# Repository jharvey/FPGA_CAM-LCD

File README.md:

## Phase order (do not skip)

1. Cleanup / hierarchy (done / finishing)
2. Power input redesign (3×18650)
3. Camera + display connectors/sheets
4. Mechanical outline / placement
5. BOM + JLCPCB

## When unsure

- Ask before deleting anything on `power`, `usb`, `ram`, `flash`, or `wifi`.
- Prefer “mark for deletion” + commit message over silent large deletes.
- Reference `ROADMAP.md` for locked decisions.

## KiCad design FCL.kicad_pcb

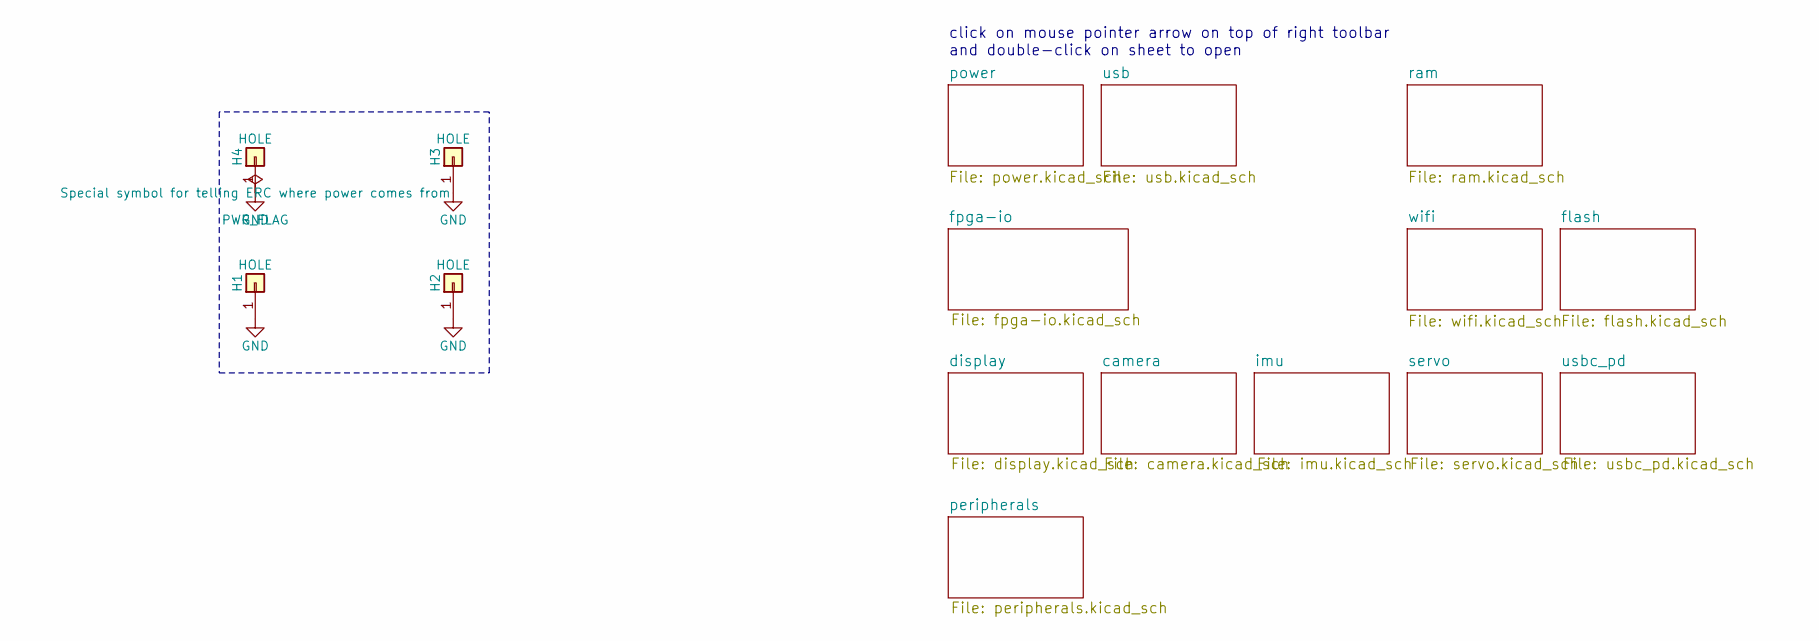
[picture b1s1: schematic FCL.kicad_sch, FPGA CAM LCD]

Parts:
H1, H2, H3, H4: HOLE; MountingHole_3.2mm_M3_ISO14580_Pad

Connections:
GND: H1.1 (Pin_1_1), H2.1, H3.1 (Pin_1_1), H4.1 (Pin_1_1); also elsewhere on the board

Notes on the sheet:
click on mouse pointer arrow on top of right toolbar and double-click on sheet to open

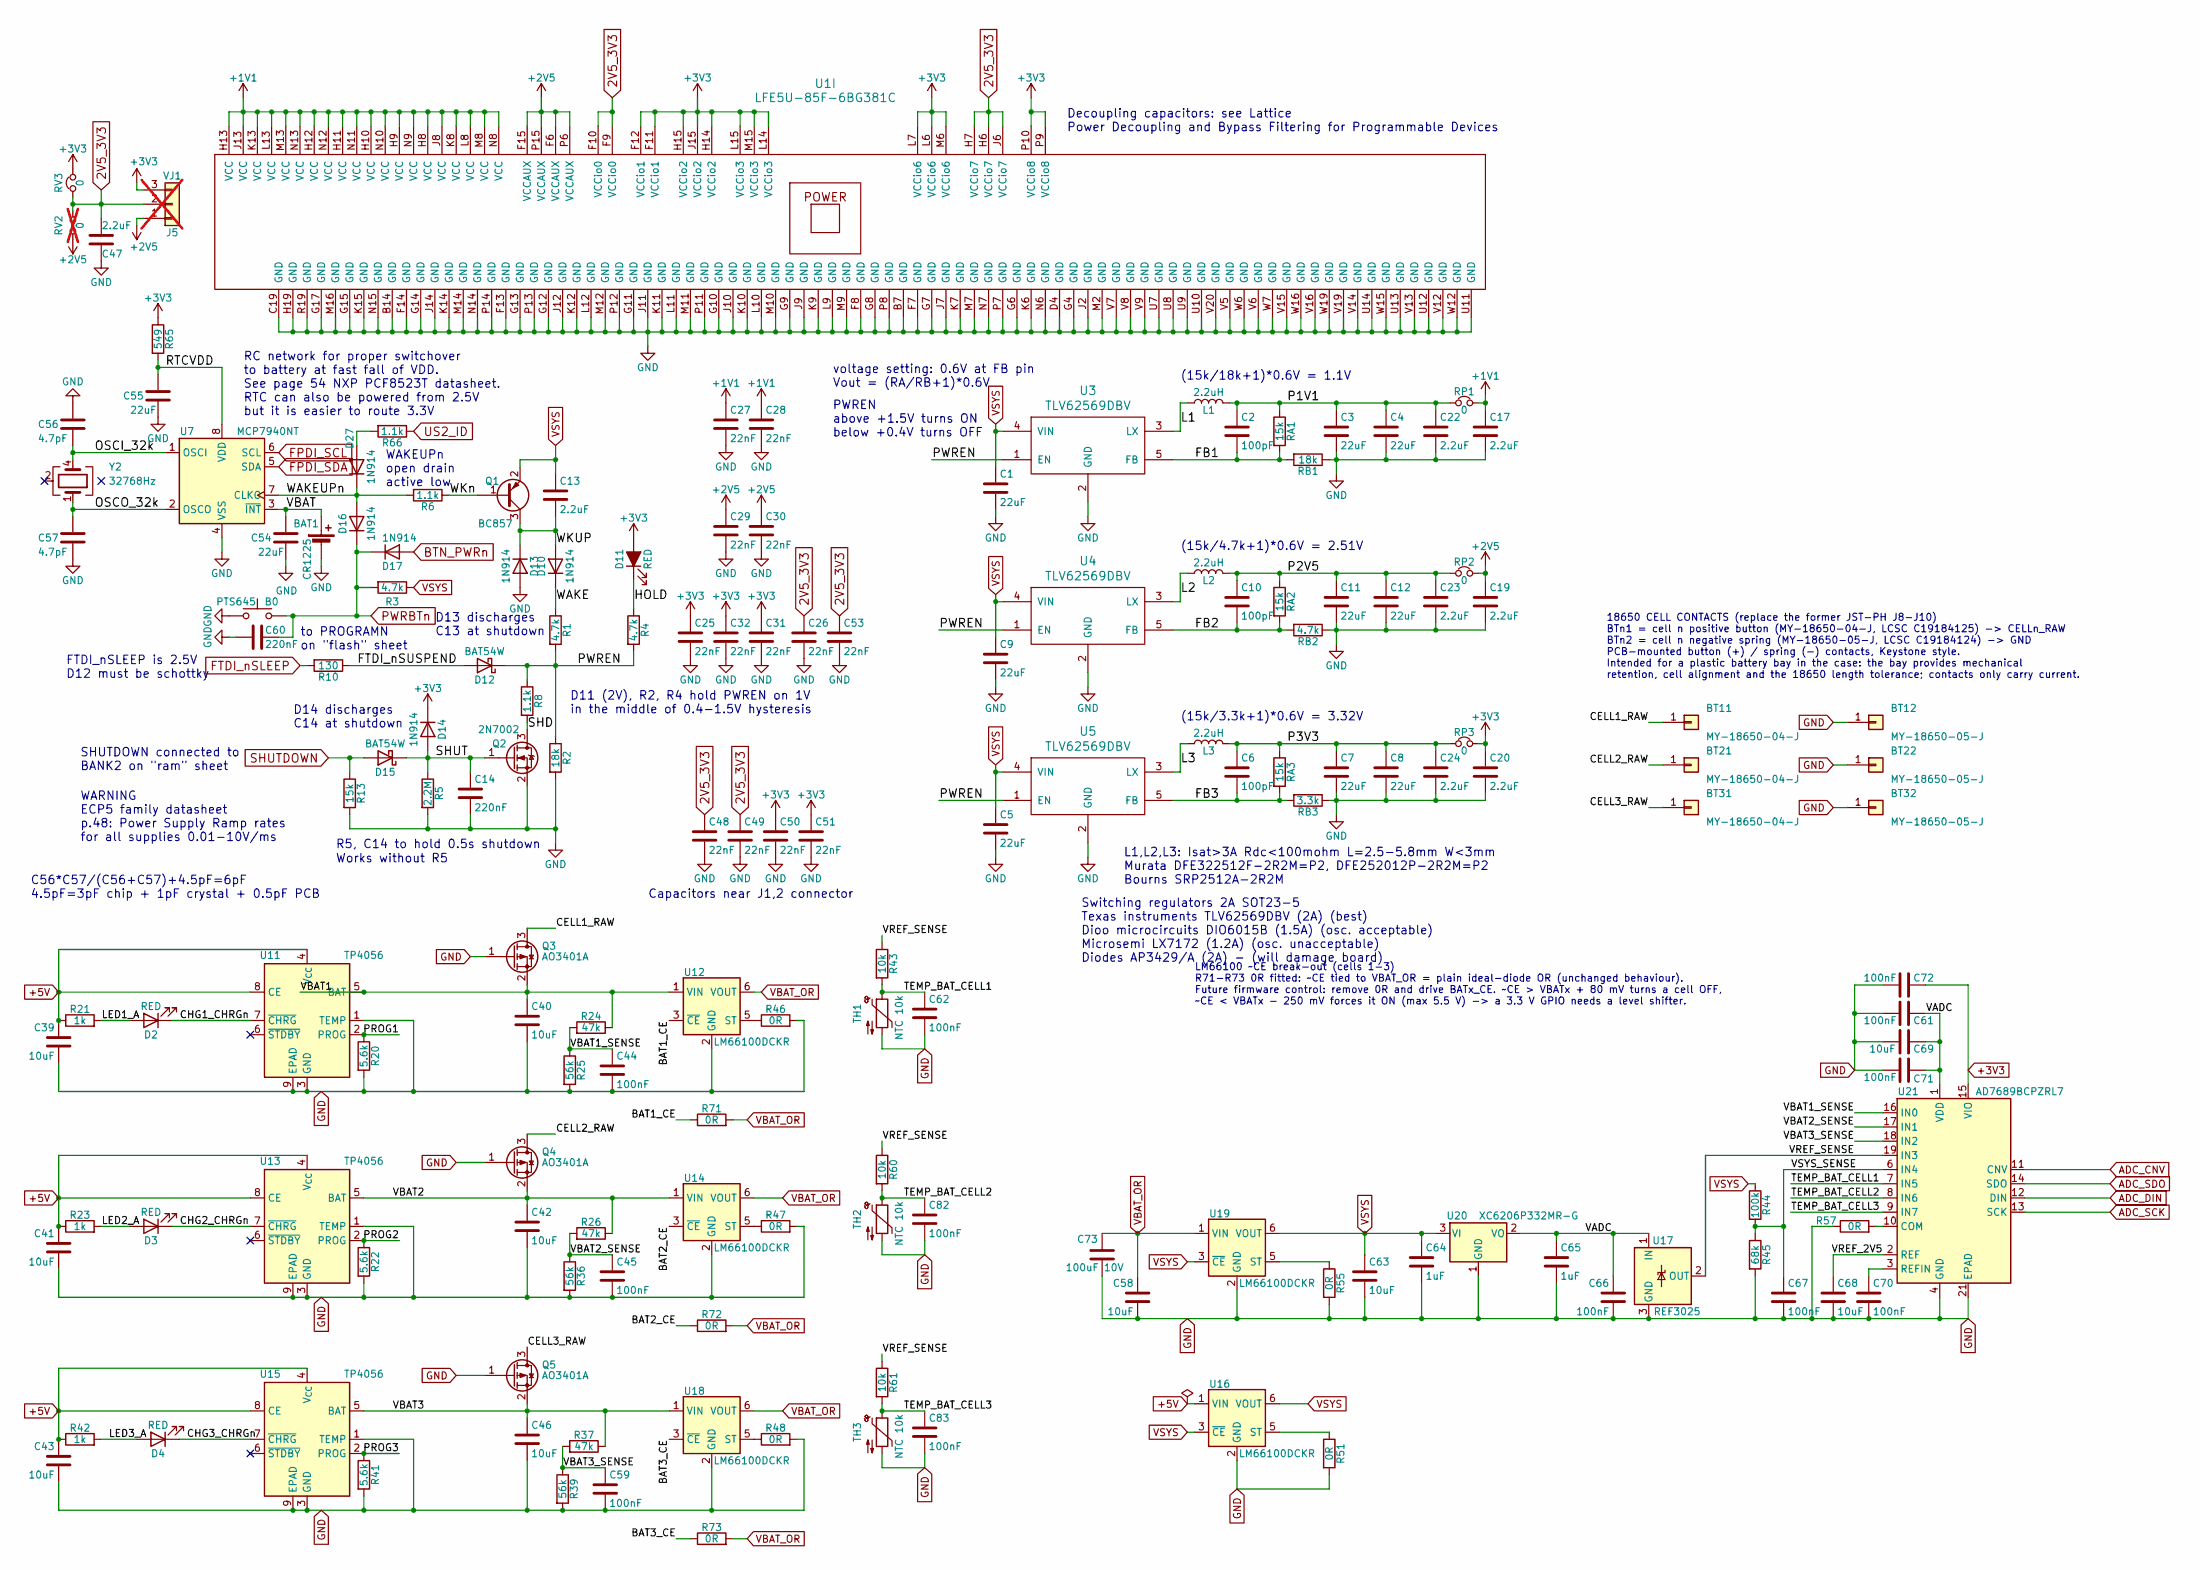
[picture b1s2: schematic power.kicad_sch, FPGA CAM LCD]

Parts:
B0: PTS645; SW_SPST_PTS645Sx43SMTR92; MPN PTS645SL50SMTR92 LFS; Mouser 611-PTS645SL50SMTR92
BAT1: CR1225; Keystone_3000_1x12mm-CoinCell; MPN 3000TR; Mouser 614-SMTM1225.TR
BT11, BT21, BT31: MY-18650-04-J; BAT-TH_MY-18650-04-J; MPN MY-18650-04-J; LCSC C19184125
BT12, BT22, BT32: MY-18650-05-J; BAT-TH_MY-18650-05-J; MPN MY-18650-05-J; LCSC C19184124
C1: 22uF; C_0805_2012Metric; MPN CC0805ZKY5V5BB226; Mouser 81-GRM21BR61A226ME1L
C2: 100pF; C_0603_1608Metric; MPN CS0603KRX7R9BB471; Mouser 581-06035A101JAT4A
C3, C4, C7, C8, C11, C12: 22uF; C_0805_2012Metric
C5, C9, C54, C55: 22uF; C_0805_2012Metric; MPN CC0805ZKY5V5BB226
C6, C10: 100pF; C_0603_1608Metric
C13: 2.2uF; C_0805_2012Metric; MPN CC0805MRX5R6BB225; Mouser 187-CL21B225KOFNNNG
C14: 220nF; C_0603_1608Metric; MPN CC0603KRX7R8BB224; Mouser 603-CC603KRX7R6BB224
C17, C19, C20, C22, C23, C24: 2.2uF; C_0805_2012Metric
C25: 22nF; C_0603_1608Metric; MPN CC0603JRX7R8BB223; Mouser 603-CC603KRX7R7BB223
C26, C27, C28, C29, C30, C31, C32, C48, C49, C50, C51, C53: 22nF; C_0603_1608Metric; MPN CX0603MRX7R8BB223
C39, C40, C41, C42, C43, C46, C58, C63, C68, C69: 10uF; C_0805_2012Metric; LCSC C15850
C44, C45, C59, C61, C62, C66, C67, C70, C71, C72, C82, C83: 100nF; C_0402_1005Metric; LCSC C1525
C47: 2.2uF; C_0805_2012Metric; MPN CC0805MRX5R6BB225
C56: 4.7pF; C_0603_1608Metric; MPN CC0603CRNPO9BN3R3; Mouser 603-CC603CPNPO9BN4R7
C57: 4.7pF; C_0603_1608Metric
C60: 220nF; C_0603_1608Metric
C64, C65: 1uF; C_0603_1608Metric; LCSC C15849
C73: 100uF 10V; C_1210_3225Metric; MPN CL32A107MPVNNNE; LCSC C23742
D2, D3, D4: RED; LED_0603_1608Metric; LCSC C2286
D10, D13, D14, D17, D27: 1N914; D_SOD-323_HandSoldering
D11: RED; LED_0805_2012Metric
D12: BAT54W; D_SOD-323_HandSoldering
D15: BAT54W; D_SOD-323_HandSoldering; MPN NSR0530HT1G; Mouser 771-BAT54J115
D16: 1N914; D_SOD-323_HandSoldering; MPN 1N4148WS; Mouser 241-1N4148WSR100001
J5: VJ1; PinHeader_1x03_P2.54mm_Vertical; not fitted
L1: 2.2uH; L_1008_1210; MPN DFE322512F-2R2M=P2; Mouser 81-DFE322512F-2R2MP2
L2, L3: 2.2uH; L_1008_1210
Q1: BC857; SOT-23; MPN BC857; Mouser 583-BC856A-T
Q2: 2N7002; SOT-23; MPN 2N7002P,215; Mouser 512-2N7002L
Q3, Q4, Q5: AO3401A; SOT-23; LCSC C15127
R1: 4.7k; R_0603_1608Metric; MPN AC0603FR-104K7L; Mouser 755-SFR03EZPF4701
R2: 18k; R_0603_1608Metric
R3, R4: 4.7k; R_0603_1608Metric; MPN AC0603FR-104K7L
R5: 2.2M; R_0603_1608Metric; MPN RC0603FR-132M2L; Mouser 603-AC0603FR-072M2L
R6, R8, R66: 1.1k; R_0603_1608Metric
R10: 130; R_0603_1608Metric
R13: 15k; R_0603_1608Metric
R20, R22, R41: 5.6k; R_0603_1608Metric; LCSC C23189
R21, R23, R42: 1k; R_0603_1608Metric; LCSC C21190
R24, R26, R37: 47k; R_0603_1608Metric; LCSC C25819
R25, R36, R39: 56k; R_0603_1608Metric; LCSC C23206
R43, R60, R61: 10k; R_0402_1005Metric; LCSC C25744
R44: 100k; R_0603_1608Metric; LCSC C25803
R45: 68k; R_0603_1608Metric; LCSC C23231
R46, R47, R48, R51, R55, R57, R71, R72, R73: 0R; R_0603_1608Metric; MPN 0603WAF0000T5E; LCSC C21189
R65: 549; R_0603_1608Metric
RA1: 15k; R_0603_1608Metric; MPN RC0603FR-1015KL
RA2, RA3: 15k; R_0603_1608Metric
RB1: 18k; R_0603_1608Metric; MPN RC0603FR-1018KL; Mouser 71-CRCW060318K0FKEAC
RB2: 4.7k; R_0603_1608Metric; MPN AC0603FR-104K7L
RB3: 3.3k; R_0603_1608Metric; MPN RT0603FRE073K3L; Mouser 603-RC0603FR-073K3L
RP1: 0; R_0805_Jumper_NC_NetTie; Mouser_URL www.mouser.com
RP2, RP3: 0; R_0805_Jumper_NC_NetTie
RV2: 0; R_0805_2012Metric_Pad1.20x1.40mm_HandSolder; not fitted
RV3: 0; R_0805_2012Metric_Pad1.20x1.40mm_HandSolder; MPN RC0805JR-070RL; Mouser 71-RCG08050000Z0EA
TH1, TH2, TH3: NTC 10k; R_0603_1608Metric; LCSC C13564
U1: LFE5U-85F-6BG381C; BGA-381_pitch0.8mm_dia0.4mm; MPN LFE5U-85F-6BG381C
U3: TLV62569DBV; TSOT-25; MPN TLV62569DBVR; Mouser 453-DIO6015BCST5
U4, U5: TLV62569DBV; TSOT-25; MPN TLV62569DBVR; Mouser 595-TLV62569DBVR
U7: MCP7940NT; SOT96-1; MPN MCP7940NT-I/SN; Mouser 579-MCP7940NT-I/SN
U11, U13, U15: TP4056; SOIC-8-1EP_3.9x4.9mm_P1.27mm_EP2.41x3.3mm_ThermalVias; LCSC C16581
U12, U14, U16, U18, U19: LM66100DCKR; SOT-363_SC-70-6; LCSC C2869734
U17: REF3025; SOT-23; MPN REF3025AIDBZT; LCSC C96625
U20: XC6206P332MR-G; SOT-23; MPN XC6206P332MR-G; LCSC C5446
U21: AD7689BCPZRL7; LFCSP-20-1EP_4x4mm_P0.5mm_EP2.6x2.6mm; MPN AD7689BCPZRL7; LCSC C706705
Y2: 32768Hz; Crystal_SMD_ABS07; MPN LFXTAL016178REEL; Mouser 520-.327-6-34BT

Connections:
2V5_3V3: C26.1, C47.1, C48.1, C49.1, C53.1, J5.2, RV2.2, RV3.1, U1.F9 (VCCio0), U1.F10 (VCCio0), U1.H6 (VCCio7), U1.H7 (VCCio7), U1.J6 (VCCio7)
+1V1: C17.1, C27.1, C28.1, RP1.2, U1.H8 (VCC), U1.H9 (VCC), U1.H10 (VCC), U1.H11 (VCC), U1.H12 (VCC), U1.H13 (VCC), U1.J8 (VCC), U1.J13 (VCC), U1.K8 (VCC), U1.K13 (VCC), U1.L8 (VCC), U1.L13 (VCC), U1.M8 (VCC), U1.M13 (VCC), U1.N8 (VCC), U1.N9 (VCC), U1.N10 (VCC), U1.N11 (VCC), U1.N12 (VCC), U1.N13 (VCC); also elsewhere on the board
+2V5: C19.1, C29.1, C30.1, J5.1, RP2.2, RV2.1, U1.F6 (VCCAUX), U1.F15 (VCCAUX), U1.P6 (VCCAUX), U1.P15 (VCCAUX); also elsewhere on the board
+3V3: C20.1, C25.1, C31.1, C32.1, C50.1, C51.1, C72.1, D11.2 (A), D14.1 (K), J5.3, R65.1, RP3.2, RV3.2, U1.F11 (VCCio1), U1.F12 (VCCio1), U1.H14 (VCCio2), U1.H15 (VCCio2), U1.J15 (VCCio2), U1.L6 (VCCio6), U1.L7 (VCCio6), U1.L14 (VCCio3), U1.L15 (VCCio3), U1.M6 (VCCio6), U1.M15 (VCCio3), U1.P9 (VCCio8), U1.P10 (VCCio8), U21.15 (VIO); also elsewhere on the board
+5V: C39.1, C41.1, C43.1, R21.1, R23.1, R42.1, U11.4 (V_{CC}), U11.8 (CE), U13.4 (V_{CC}), U13.8 (CE), U15.4 (V_{CC}), U15.8 (CE), U16.1 (VIN); also elsewhere on the board
/power/BAT1_CE: R71.1, U12.3 (~CE)
/power/BAT2_CE: R72.1, U14.3 (~CE)
/power/BAT3_CE: R73.1, U18.3 (~CE)
/power/CELL1_RAW: BT11.1 (Pin_1_1), Q3.3 (D)
/power/CELL2_RAW: BT21.1 (Pin_1_1), Q4.3 (D)
/power/CELL3_RAW: BT31.1 (Pin_1_1), Q5.3 (D)
/power/CHG1_CHRGn: D2.1 (K), U11.7 (~CHRG)
/power/CHG2_CHRGn: D3.1 (K), U13.7 (~CHRG)
/power/CHG3_CHRGn: D4.1 (K), U15.7 (~CHRG)
/power/FB1: C2.2, RA1.2, RB1.2, U3.5 (FB)
/power/FB2: C10.2, RA2.2, RB2.2, U4.5 (FB)
/power/FB3: C6.2, RA3.2, RB3.2, U5.5 (FB)
/power/FTDI_nSUSPEND: D12.2 (A), R10.1
/power/HOLD: D11.1 (K), R4.1
/power/L1: L1.1, U3.3 (LX)
/power/L2: L2.1, U4.3 (LX)
/power/L3: L3.1, U5.3 (LX)
/power/LED1_A: D2.2 (A), R21.2
/power/LED2_A: D3.2 (A), R23.2
/power/LED3_A: D4.2 (A), R42.2
/power/OSCI_32k: C56.2, U7.1 (OSCI), Y2.4
/power/OSCO_32k: C57.2, U7.2 (OSCO), Y2.1
/power/P1V1: C2.1, C3.1, C4.1, C22.1, L1.2, RA1.1, RP1.1
/power/P2V5: C10.1, C11.1, C12.1, C23.1, L2.2, RA2.1, RP2.1
/power/P3V3: C6.1, C7.1, C8.1, C24.1, L3.2, RA3.1, RP3.1
/power/PROG1: R20.1, U11.2 (PROG)
/power/PROG2: R22.1, U13.2 (PROG)
/power/PROG3: R41.1, U15.2 (PROG)
/power/PWREN: D12.1 (K), R1.2, R2.1, R4.2, R8.1, U3.1 (EN), U4.1 (EN), U5.1 (EN)
/power/RTCVDD: C55.1, R65.2, U7.8 (VDD)
/power/SHD: Q2.3 (D), R8.2
/power/SHUT: C14.1, D14.2 (A), D15.1 (K), Q2.1 (G), R5.1
/power/TEMP_BAT_CELL1: C62.1, R43.2, TH1.1, U21.7 (IN5)
/power/TEMP_BAT_CELL2: C82.1, R60.2, TH2.1, U21.8 (IN6)
/power/TEMP_BAT_CELL3: C83.1, R61.2, TH3.1, U21.9 (IN7)
/power/VADC: C61.1, C65.1, C66.1, C69.1, C71.1, U17.1 (IN), U20.2 (VO), U21.1 (VDD), U21.20 (VDD)
/power/VBAT: BAT1.1 (+), C54.1, U7.3 (~INT)
/power/VBAT1: C40.1, Q3.2 (S), R24.1, U11.5 (BAT), U12.1 (VIN)
/power/VBAT1_SENSE: C44.1, R24.2, R25.1, U21.16 (IN0)
/power/VBAT2: C42.1, Q4.2 (S), R26.1, U13.5 (BAT), U14.1 (VIN)
/power/VBAT2_SENSE: C45.1, R26.2, R36.1, U21.17 (IN1)
/power/VBAT3: C46.1, Q5.2 (S), R37.1, U15.5 (BAT), U18.1 (VIN)
/power/VBAT3_SENSE: C59.1, R37.2, R39.1, U21.18 (IN2)
/power/VREF_2V5: C68.1, U21.2 (REF)
/power/VREF_SENSE: R43.1, R60.1, R61.1, U17.2 (OUT), U21.19 (IN3)
/power/VSYS_SENSE: C67.1, R44.2, R45.1, U21.6 (IN4)
/power/WAKE: D10.1 (K), R1.1
/power/WAKEUPn: D16.2 (A), D27.1 (K), R6.2, U7.7 (CLKO)
/power/WKUP: C13.2, D10.2 (A), D13.1 (K), Q1.3 (C)
/power/WKn: Q1.1 (B), R6.1
ADC_CNV: U21.11 (CNV); also elsewhere on the board
ADC_DIN: U21.12 (DIN); also elsewhere on the board
ADC_SCK: U21.13 (SCK); also elsewhere on the board
ADC_SDO: U21.14 (SDO); also elsewhere on the board
BTN_PWRn: D17.2 (A); also elsewhere on the board
FPDI_SCL: U7.6 (SCL); also elsewhere on the board
FPDI_SDA: U7.5 (SDA); also elsewhere on the board
FTDI_nSLEEP: R10.2
GND: B0.2, BAT1.2 (-), BT12.1 (Pin_1_1), BT22.1 (Pin_1_1), BT32.1 (Pin_1_1), C1.2, C3.2, C4.2, C5.2, C7.2, C8.2, C9.2, C11.2, C12.2, C14.2, C17.2, C19.2, C20.2, C22.2, C23.2, C24.2, C25.2, C26.2, C27.2, C28.2, C29.2, C30.2, C31.2, C32.2, C39.2, C40.2, C41.2, C42.2, C43.2, C44.2, C45.2, C46.2, C47.2, C48.2, C49.2, C50.2, C51.2, C53.2, C54.2, C55.2, C56.1, C57.1, C58.2, C59.2, C60.2, C61.2, C62.2, C63.2, C64.2, C65.2, C66.2, C67.2, C68.2, C69.2, C70.2, C71.2, C72.2, C73.2, C82.2, C83.2, D13.2 (A), Q2.2 (S), Q3.1 (G), Q4.1 (G), Q5.1 (G), R2.2, R5.2, R13.2, R20.2, R22.2, R25.2, R36.2, R39.2, R41.2, R45.2, R46.2, R47.2, R48.2, R51.2, R55.2, R57.1, RB1.1, RB2.1, RB3.1, TH1.2, TH2.2, TH3.2, U1.B7 (GND), U1.B14 (GND), U1.C19 (GND), U1.D4 (GND), U1.F7 (GND), U1.F8 (GND), U1.F13 (GND), U1.F14 (GND), U1.G4 (GND), U1.G6 (GND), U1.G7 (GND), U1.G8 (GND), U1.G9 (GND), U1.G10 (GND), U1.G11 (GND), U1.G12 (GND), U1.G13 (GND), U1.G14 (GND), U1.G15 (GND), U1.G17 (GND), U1.H19 (GND), U1.J2 (GND), U1.J7 (GND), U1.J9 (GND), U1.J10 (GND), U1.J11 (GND), U1.J12 (GND), U1.J14 (GND), U1.K6 (GND), U1.K7 (GND), U1.K9 (GND), U1.K10 (GND), U1.K11 (GND), U1.K12 (GND), U1.K14 (GND), U1.K15 (GND), U1.L9 (GND), U1.L10 (GND), U1.L11 (GND), U1.L12 (GND), U1.M2 (GND), U1.M7 (GND), U1.M9 (GND), U1.M10 (GND), U1.M11 (GND), U1.M12 (GND), U1.M14 (GND), U1.M16 (GND), U1.N6 (GND), U1.N7 (GND), U1.N14 (GND), U1.N15 (GND), U1.P7 (GND), U1.P8 (GND), U1.P11 (GND), U1.P12 (GND), U1.P13 (GND), U1.P14 (GND), U1.R19 (GND), U1.U7 (GND), U1.U8 (GND), U1.U9 (GND), U1.U10 (GND), U1.U11 (GND), U1.U12 (GND), U1.U13 (GND), U1.U14 (GND), U1.V5 (GND), U1.V6 (GND), U1.V7 (GND), U1.V8 (GND), U1.V9 (GND), U1.V12 (GND), U1.V13 (GND), U1.V14 (GND), U1.V15 (GND), U1.V16 (GND), U1.V19 (GND), U1.V20 (GND), U1.W6 (GND), U1.W7 (GND), U1.W12 (GND), U1.W15 (GND), U1.W16 (GND), U1.W19 (GND), U3.2 (GND), U4.2 (GND), U5.2 (GND), U7.4 (VSS), U11.1 (TEMP), U11.3 (GND), U11.9 (EPAD), U12.2 (GND), U13.1 (TEMP), U13.3 (GND), U13.9 (EPAD), U14.2 (GND), U15.1 (TEMP), U15.3 (GND), U15.9 (EPAD), U16.2 (GND), U17.3 (GND), U18.2 (GND), U19.2 (GND), U20.1 (GND), U21.4 (GND), U21.5 (GND), U21.21 (EPAD); also elsewhere on the board
unnamed: D27.2 (A), R66.2
unnamed: R46.1, U12.5 (ST)
unnamed: R47.1, U14.5 (ST)
unnamed: R51.1, U16.5 (ST)
unnamed: R48.1, U18.5 (ST)
unnamed: R55.1, U19.5 (ST)
unnamed: R57.2, U21.10 (COM)
unnamed: C70.1, U21.3 (REFIN)
PWRBTn: B0.1, C60.1, D16.1 (K), D17.1 (K), R3.2; also elsewhere on the board
SHUTDOWN: D15.2 (A), R13.1; also elsewhere on the board
US2_ID: R66.1
VBAT_OR: C58.1, C73.1, R71.2, R72.2, R73.2, U12.6 (VOUT), U14.6 (VOUT), U18.6 (VOUT), U19.1 (VIN)
VSYS: C1.1, C5.1, C9.1, C13.1, C63.1, C64.1, Q1.2 (E), R3.1, R44.1, U3.4 (VIN), U4.4 (VIN), U5.4 (VIN), U16.3 (~CE), U16.6 (VOUT), U19.3 (~CE), U19.6 (VOUT), U20.3 (VI); also elsewhere on the board

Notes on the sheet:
FTDI_nSLEEP is 2.5V D12 must be schottky
voltage setting: 0.6V at FB pin Vout = (RA/RB+1)*0.6V
Switching regulators 2A SOT23-5 Texas instruments TLV62569DBV (2A) (best) Dioo microcircuits DIO6015B (1.5A) (osc. acceptable) Microsemi LX7172 (1.2A) (osc. unacceptable) Diodes AP3429/A (2A) - (will damage board)
18650 CELL CONTACTS (replace the former JST-PH J8-J10) BTn1 = cell n positive button (MY-18650-04-J, LCSC C19184125) -> CELLn_RAW BTn2 = cell n negative spring (MY-18650-05-J, LCSC C19184124) -> GND PCB-mounted button (+) / spring (-) contacts, Keystone style. Intended for a plastic battery bay in 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
Works without R5
L1,L2,L3: Isat>3A Rdc<100mohm L=2.5-5.8mm W<3mm Murata DFE322512F-2R2M=P2, DFE252012P-2R2M=P2 Bourns SRP2512A-2R2M
Decoupling capacitors: see Lattice Power Decoupling and Bypass Filtering for Programmable Devices
LM66100 ~CE break-out (cells 1-3) R71-R73 0R fitted: ~CE tied to VBAT_OR = plain ideal-diode OR (unchanged behaviour). Future firmware control: remove 0R and drive BATx_CE. ~CE > VBATx + 80 mV turns a cell OFF, ~CE < VBATx - 250 mV forces it ON (max 5.5 V) -> a 3.3 V GPIO needs a level shifter.
R5, C14 to hold 0.5s shutdown
WARNING ECP5 family datasheet p.48: Power Supply Ramp rates for all supplies 0.01-10V/ms
to PROGRAMN on "flash" sheet
SHUTDOWN connected to BANK2 on "ram" sheet
(15k/3.3k+1)*0.6V = 3.32V
(15k/4.7k+1)*0.6V = 2.51V
RC network for proper switchover to battery at fast fall of VDD. See page 54 NXP PCF8523T datasheet. RTC can also be powered from 2.5V but it is easier to route 3.3V
D14 discharges C14 at shutdown
(15k/18k+1)*0.6V = 1.1V
D11 (2V), R2, R4 hold PWREN on 1V in the middle of 0.4-1.5V hysteresis
Capacitors near J1,2 connector
PWREN above +1.5V turns ON below +0.4V turns OFF
C56*C57/(C56+C57)+4.5pF=6pF 4.5pF=3pF chip + 1pF crystal + 0.5pF PCB
WAKEUPn open drain active low
D13 discharges C13 at shutdown

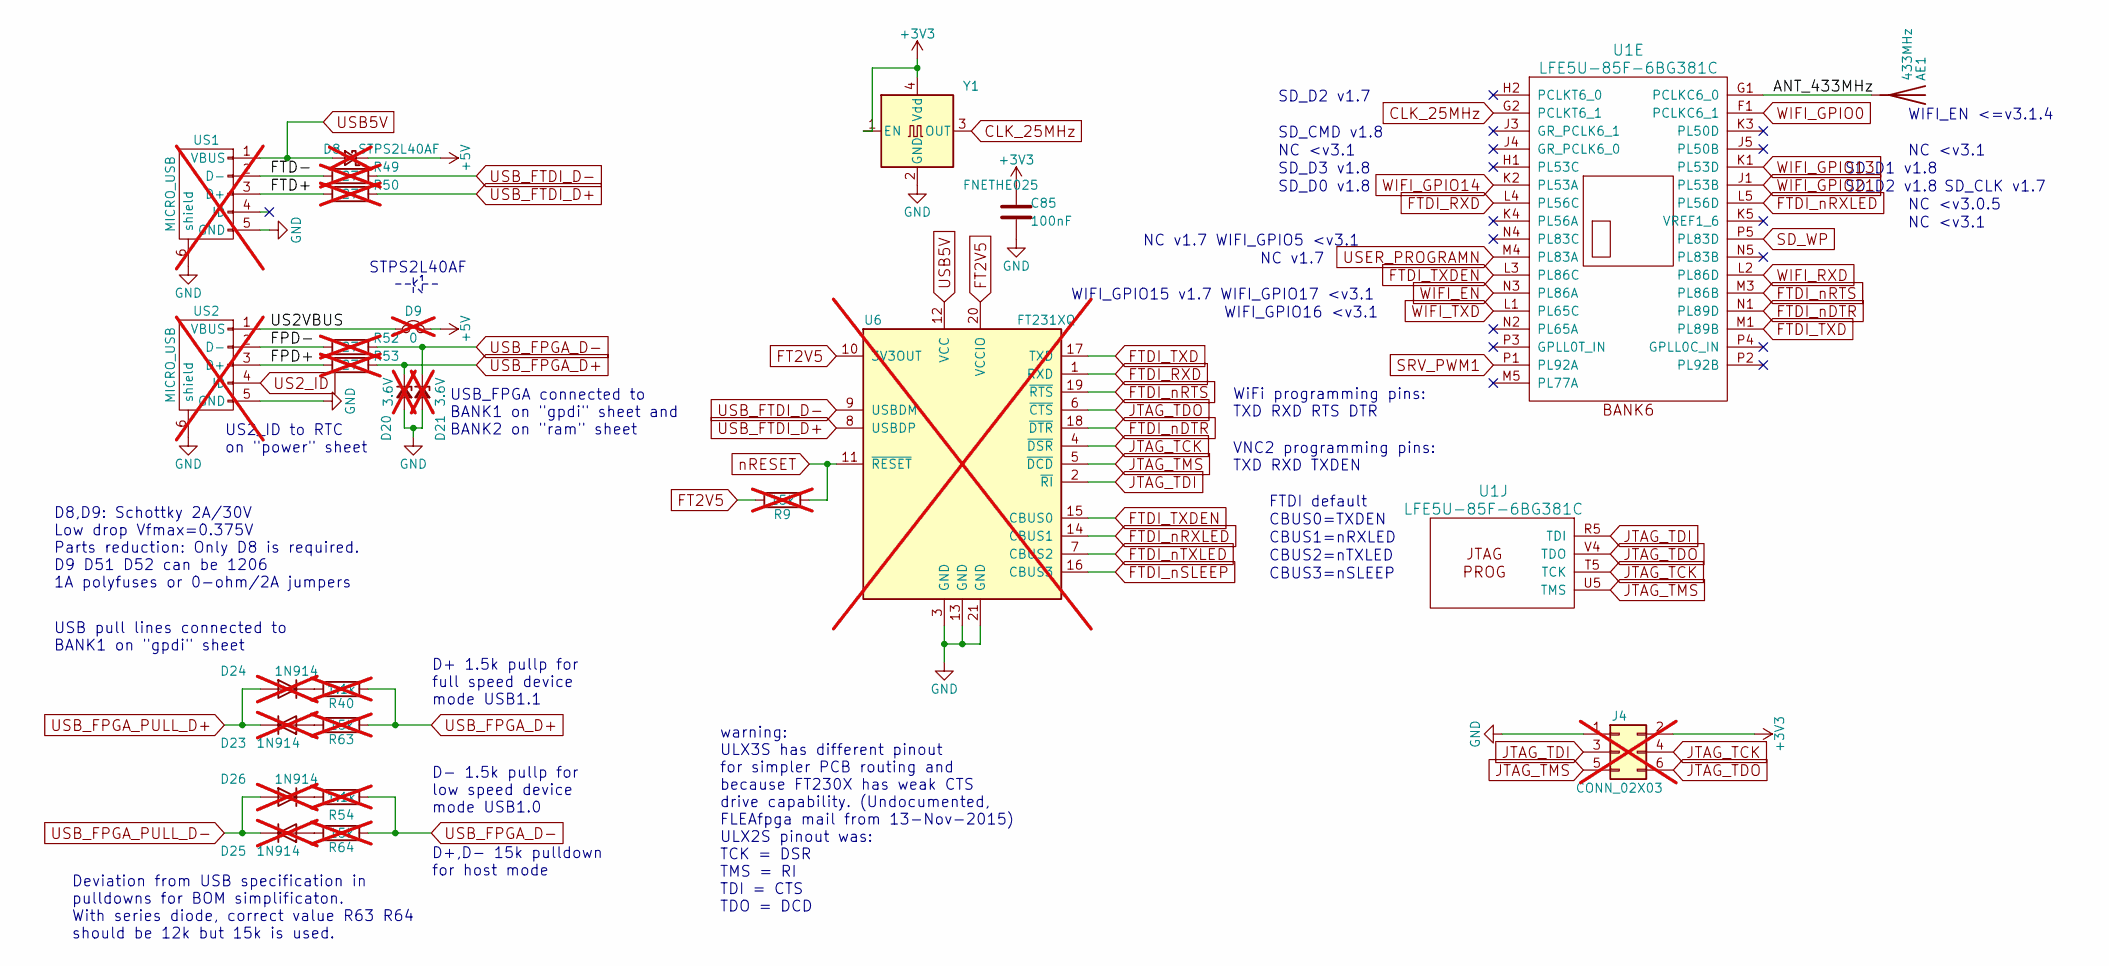
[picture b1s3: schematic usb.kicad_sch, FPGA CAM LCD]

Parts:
AE1: 433MHz; TestPoint_Pad_D1.0mm
C85: 100nF; C_0402_1005Metric; LCSC C1525
D8: STPS2L40AF; D_SMA; MPN STPS2L30AF; Mouser 511-STPS2L40AF; not fitted
D9: 0; D_SMA_Jumper_NC; MPN2 STPS2L30AF; not fitted
D20, D21: 3.6V; D_SOD-323_HandSoldering; MPN BZT52C3V6S; Mouser 833-BZT52C3V6S-TP; not fitted
D23, D24, D25: 1N914; D_SOD-323_HandSoldering; not fitted
D26: 1N914; D_SOD-323_HandSoldering; MPN 1N4148WS; not fitted
J4: CONN_02X03; Tag-Connect_TC2030-IDC-FP_2x03_P1.27mm_Vertical; not fitted
R9: 15k; R_0603_1608Metric; MPN RC0603FR-0715KL; Mouser 603-AC0603FR-1015KL; not fitted
R40, R54: 1.1k; R_0603_1608Metric; not fitted
R49: 27; R_0603_1608Metric; MPN AC0603JR-0727RL; Mouser 603-AC0603JR-0727RL; not fitted
R50, R52, R53: 27; R_0603_1608Metric; MPN AC0603JR-0727RL; not fitted
R63, R64: 15k; R_0603_1608Metric; not fitted
U1: LFE5U-85F-6BG381C; BGA-381_pitch0.8mm_dia0.4mm; MPN LFE5U-85F-6BG381C
U6: FT231XQ; FT231X-QFN-20-1EP_4x4mm_P0.5mm_EP2x2mm; MPN FT231XQ; Mouser 895-FT231XQ-R; not fitted
US1: MICRO_USB; USB-MICRO-B-FCI-10118192-0001LF; MPN 10118192-0001LF; Mouser 649-10118192-0001LF; not fitted
US2: MICRO_USB; USB-MICRO-B-FCI-10118192-0001LF; not fitted
Y1: FNETHE025; Crystal_SMD_7050_4Pads; MPN FNETHE025; Mouser 729-FNETHE025

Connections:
+3V3: C85.1, J4.2, Y1.1 (EN), Y1.4 (Vdd); also elsewhere on the board
/usb/ANT_433MHz: AE1.1 (A_1), U1.G1 (PCLKC6_0)
CLK_25MHz: U1.G2 (PCLKT6_1), Y1.3 (OUT)
FTDI_RXD: U1.L4 (PL56C), U6.1 (RXD)
FTDI_TXD: U1.M1 (PL89B), U6.17 (TXD)
FTDI_TXDEN: U1.L3 (PL86C), U6.15 (CBUS0)
FTDI_nDTR: U1.N1 (PL89D), U6.18 (~DTR)
FTDI_nRTS: U1.M3 (PL86B), U6.19 (~RTS)
FTDI_nRXLED: U1.L5 (PL56D), U6.14 (CBUS1)
GND: C85.2, D20.2 (A), D21.2 (A), J4.1, U6.3 (GND), U6.13 (GND), U6.21 (GND), US1.5 (GND), US1.6 (shield), US2.5 (GND), US2.6 (shield), Y1.2 (GND); also elsewhere on the board
JTAG_TCK: J4.4, U1.T5 (TCK), U6.4 (~DSR); also elsewhere on the board
JTAG_TDI: J4.3, U1.R5 (TDI), U6.2 (~RI); also elsewhere on the board
JTAG_TDO: J4.6, U1.V4 (TDO), U6.6 (~CTS); also elsewhere on the board
JTAG_TMS: J4.5, U1.U5 (TMS), U6.5 (~DCD); also elsewhere on the board
unnamed: D8.1 (K), D9.2
unnamed: D8.2 (A), U6.12 (VCC), US1.1 (VBUS)
unnamed: D9.1, US2.1 (VBUS)
unnamed: D20.1 (K), R40.2, R53.1, R63.2
unnamed: D21.1 (K), R52.1, R54.1, R64.2
unnamed: D23.1 (K), D24.2 (A)
unnamed: D23.2 (A), R63.1
unnamed: D24.1 (K), R40.1
unnamed: D25.1 (K), D26.2 (A)
unnamed: D25.2 (A), R64.1
unnamed: D26.1 (K), R54.2
unnamed: R9.1, U6.11 (~RESET)
unnamed: R9.2, U6.10 (3V3OUT), U6.20 (VCCIO)
unnamed: R49.1, U6.9 (USBDM)
unnamed: R49.2, US1.2 (D-)
unnamed: R50.1, U6.8 (USBDP)
unnamed: R50.2, US1.3 (D+)
unnamed: R52.2, US2.2 (D-)
unnamed: R53.2, US2.3 (D+)
SD_WP: U1.P5 (PL83D)
SRV_PWM1: U1.P1 (PL92A); also elsewhere on the board
USER_PROGRAMN: U1.M4 (PL83A); also elsewhere on the board
WIFI_EN: U1.N3 (PL86A); also elsewhere on the board
WIFI_GPIO0: U1.F1 (PCLKC6_1); also elsewhere on the board
WIFI_GPIO13: U1.K1 (PL53D); also elsewhere on the board
WIFI_GPIO14: U1.K2 (PL53A); also elsewhere on the board
WIFI_GPIO21: U1.J1 (PL53B); also elsewhere on the board
WIFI_RXD: U1.L2 (PL86D); also elsewhere on the board
WIFI_TXD: U1.L1 (PL65C); also elsewhere on the board

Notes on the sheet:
WIFI_EN <=v3.1.4
USB pull lines connected to BANK1 on "gpdi" sheet
NC <v3.0.5
D+ 1.5k pullp for full speed device mode USB1.1
D8,D9: Schottky 2A/30V Low drop Vfmax=0.375V Parts reduction: Only D8 is required. D9 D51 D52 can be 1206 1A polyfuses or 0-ohm/2A jumpers
SD_D3 v1.8
NC v1.7
NC <v3.1
SD_D0 v1.8
CBUS0=TXDEN
WIFI_GPIO16 <v3.1
SD_CLK v1.7
VNC2 programming pins: TXD RXD TXDEN
SD_D2 v1.8
CBUS1=nRXLED
FTDI default
USB_FPGA connected to BANK1 on "gpdi" sheet and BANK2 on "ram" sheet
WiFi programming pins: TXD RXD RTS DTR
D- 1.5k pullp for low speed device mode USB1.0
SD_D1 v1.8
warning: ULX3S has different pinout for simpler PCB routing and because FT230X has weak CTS drive capability. (Undocumented, FLEAfpga mail from 13-Nov-2015) ULX2S pinout was: TCK = DSR TMS = RI TDI = CTS TDO = DCD
WIFI_GPIO15 v1.7 WIFI_GPIO17 <v3.1
SD_CMD v1.8
CBUS2=nTXLED
Deviation from USB specification in pulldowns for BOM simplificaton. With series diode, correct value R63 R64 should be 12k but 15k is used.
STPS2L40AF
NC v1.7 WIFI_GPIO5 <v3.1
CBUS3=nSLEEP
SD_D2 v1.7
US2_ID to RTC on "power" sheet
D+,D- 15k pulldown for host mode

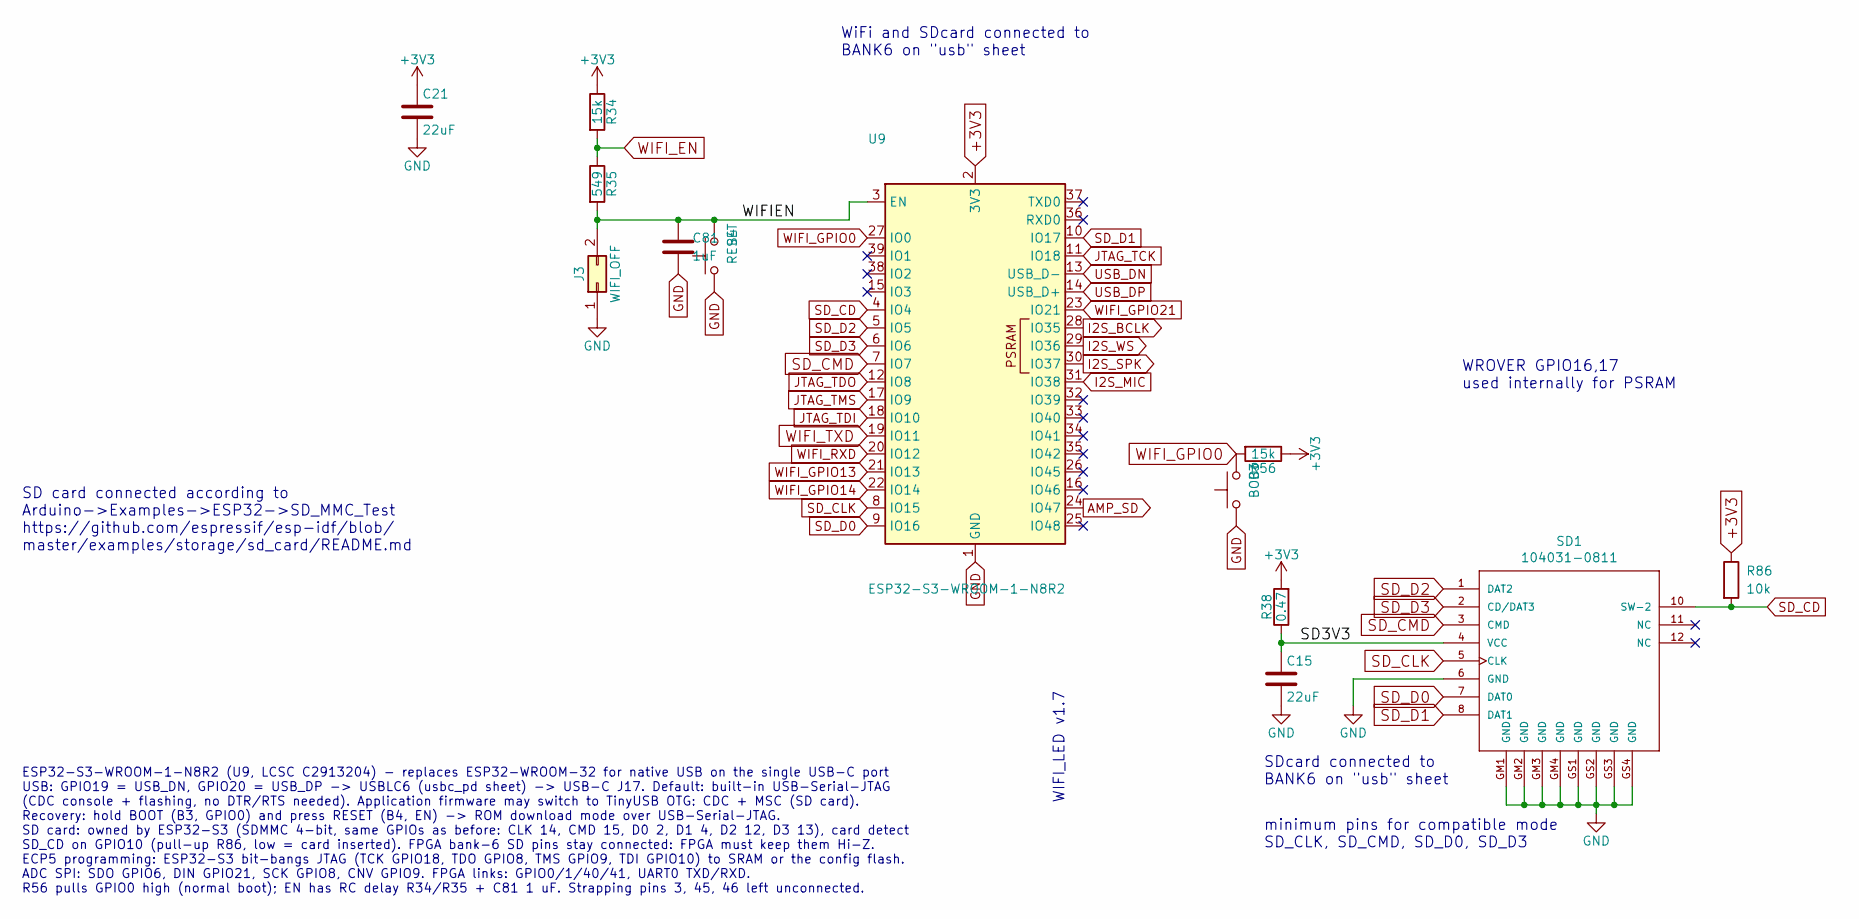
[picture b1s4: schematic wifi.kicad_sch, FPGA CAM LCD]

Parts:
B3: BOOT; SW_Push_1P1T_NO_CK_KMR2
B4: RESET; SW_Push_1P1T_NO_CK_KMR2
C15, C21: 22uF; C_0805_2012Metric; MPN CC0805ZKY5V5BB226
C81: 1uF; C_0603_1608Metric; LCSC C15849
J3: WIFI_OFF; PinHeader_1x02_P2.54mm_Vertical
R34, R56: 15k; R_0603_1608Metric
R35: 549; R_0603_1608Metric
R38: 0.47; R_0603_1608Metric; MPN 73L2R47J; Mouser 774-73L2R47J
R86: 10k; R_0402_1005Metric; LCSC C25744
SD1: 104031-0811; microSD_Molex_104031-0811_FCL; MPN 104031-0811; Mouser 538-104031-0811
U9: ESP32-S3-WROOM-1-N8R2; ESP32-S3-WROOM-1; MPN ESP32-S3-WROOM-1-N8R2; LCSC C2913204

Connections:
+3V3: C21.1, R34.1, R38.2, R56.1, R86.1, U9.2 (3V3); also elsewhere on the board
/wifi/SD3V3: C15.1, R38.1, SD1.4 (VCC)
/wifi/WIFIEN: B4.2, C81.1, J3.2, R35.2, U9.3 (EN)
AMP_SD: U9.24 (IO47); also elsewhere on the board
GND: B3.1, B4.1, C15.2, C21.2, C81.2, J3.1, SD1.6 (GND), SD1.GM1 (GND), SD1.GM2 (GND), SD1.GM3 (GND), SD1.GM4 (GND), SD1.GS1 (GND), SD1.GS2 (GND), SD1.GS3 (GND), SD1.GS4 (GND), U9.1 (GND), U9.40 (GND), U9.41 (GND); also elsewhere on the board
I2S_BCLK: U9.28 (IO35); also elsewhere on the board
I2S_MIC: U9.31 (IO38); also elsewhere on the board
I2S_SPK: U9.30 (IO37); also elsewhere on the board
I2S_WS: U9.29 (IO36); also elsewhere on the board
JTAG_TCK: U9.11 (IO18); also elsewhere on the board
JTAG_TDI: U9.18 (IO10); also elsewhere on the board
JTAG_TDO: U9.12 (IO8); also elsewhere on the board
JTAG_TMS: U9.17 (IO9); also elsewhere on the board
SD_CD: R86.2, SD1.10 (SW-2), U9.4 (IO4)
SD_CLK: SD1.5 (CLK), U9.8 (IO15); also elsewhere on the board
SD_CMD: SD1.3 (CMD), U9.7 (IO7); also elsewhere on the board
SD_D0: SD1.7 (DAT0), U9.9 (IO16); also elsewhere on the board
SD_D1: SD1.8 (DAT1), U9.10 (IO17); also elsewhere on the board
SD_D2: SD1.1 (DAT2), U9.5 (IO5); also elsewhere on the board
SD_D3: SD1.2 (CD/DAT3), U9.6 (IO6); also elsewhere on the board
USB_DN: U9.13 (USB_D-); also elsewhere on the board
USB_DP: U9.14 (USB_D+); also elsewhere on the board
WIFI_EN: R34.2, R35.1; also elsewhere on the board
WIFI_GPIO0: B3.2, R56.2, U9.27 (IO0); also elsewhere on the board
WIFI_GPIO13: U9.21 (IO13); also elsewhere on the board
WIFI_GPIO14: U9.22 (IO14); also elsewhere on the board
WIFI_GPIO21: U9.23 (IO21); also elsewhere on the board
WIFI_RXD: U9.20 (IO12); also elsewhere on the board
WIFI_TXD: U9.19 (IO11); also elsewhere on the board

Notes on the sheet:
SDcard connected to BANK6 on "usb" sheet
minimum pins for compatible mode SD_CLK, SD_CMD, SD_D0, SD_D3
WIFI_LED v1.7
SD card connected according to Arduino->Examples->ESP32->SD_MMC_Test https://github.com/espressif/esp-idf/blob/ master/examples/storage/sd_card/README.md
WROVER GPIO16,17 used internally for PSRAM
ESP32-S3-WROOM-1-N8R2 (U9, LCSC C2913204) - replaces ESP32-WROOM-32 for native USB on the single USB-C port USB: GPIO19 = USB_DN, GPIO20 = USB_DP -> USBLC6 (usbc_pd sheet) -> USB-C J17. Default: built-in USB-Serial-JTAG (CDC console + flashing, no DTR/RTS needed). Application firmware may switch to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
WiFi and SDcard connected to BANK6 on "usb" sheet

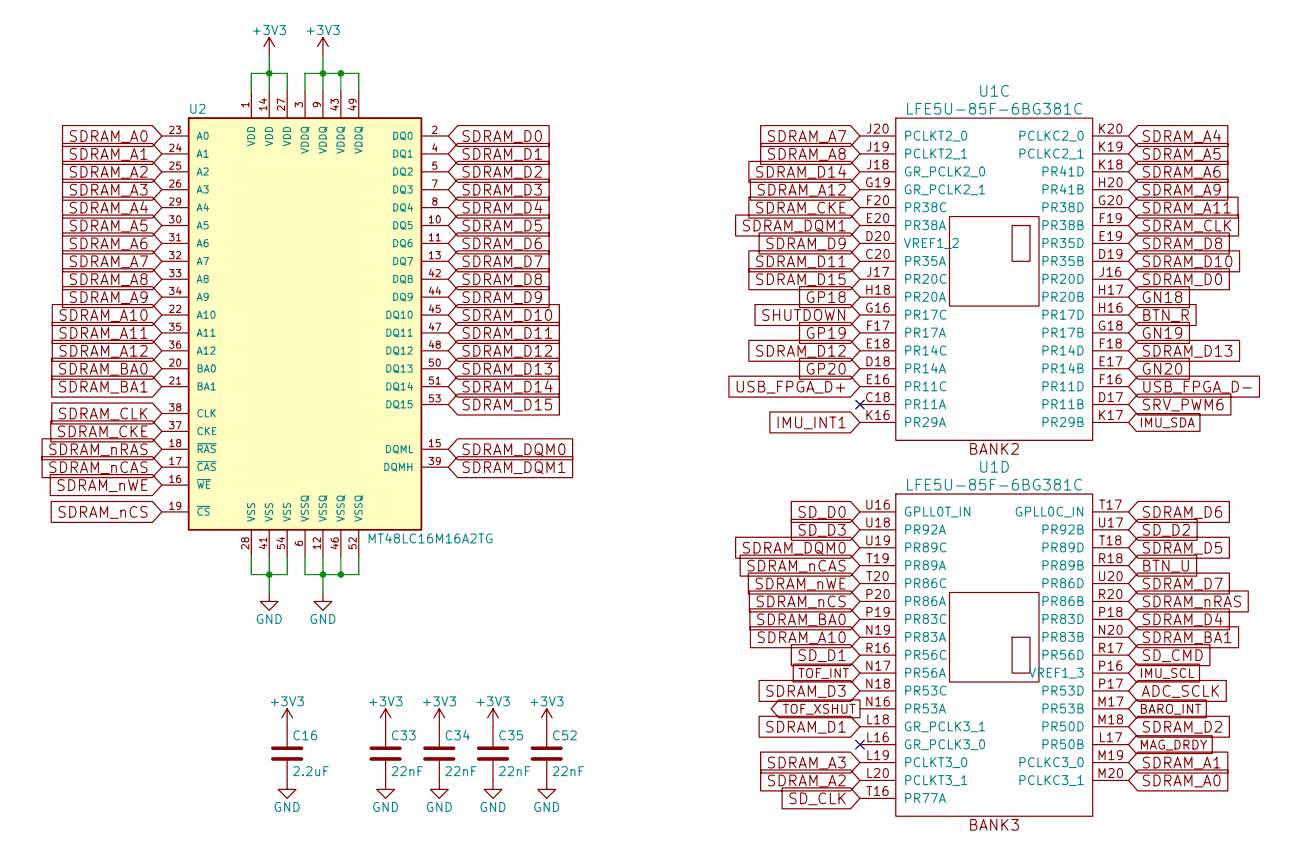
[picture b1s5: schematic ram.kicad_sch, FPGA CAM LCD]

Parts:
C16: 2.2uF; C_0805_2012Metric
C33, C34, C35, C52: 22nF; C_0603_1608Metric; MPN CX0603MRX7R8BB223
U1: LFE5U-85F-6BG381C; BGA-381_pitch0.8mm_dia0.4mm; MPN LFE5U-85F-6BG381C
U2: MT48LC16M16A2TG; TSOP54; MPN MT48LC16M16A2TG-6A; Mouser 870-IS42S16160G7TLTR

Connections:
+3V3: C16.1, C33.1, C34.1, C35.1, C52.1, U2.1 (VDD), U2.3 (VDDQ), U2.9 (VDDQ), U2.14 (VDD), U2.27 (VDD), U2.43 (VDDQ), U2.49 (VDDQ); also elsewhere on the board
ADC_SCLK: U1.P17 (PR53D)
BARO_INT: U1.M17 (PR53B); also elsewhere on the board
BTN_R: U1.H16 (PR17D)
BTN_U: U1.R18 (PR89B)
GN18: U1.H17 (PR20B)
GN19: U1.G18 (PR17B)
GN20: U1.E17 (PR14B)
GND: C16.2, C33.2, C34.2, C35.2, C52.2, U2.6 (VSSQ), U2.12 (VSSQ), U2.28 (VSS), U2.41 (VSS), U2.46 (VSSQ), U2.52 (VSSQ), U2.54 (VSS); also elsewhere on the board
GP18: U1.H18 (PR20A)
GP19: U1.F17 (PR17A)
GP20: U1.D18 (PR14A)
IMU_INT1: U1.K16 (PR29A); also elsewhere on the board
IMU_SCL: U1.P16 (VREF1_3); also elsewhere on the board
IMU_SDA: U1.K17 (PR29B); also elsewhere on the board
MAG_DRDY: U1.L17 (PR50B); also elsewhere on the board
SDRAM_A0: U1.M20 (PCLKC3_1), U2.23 (A0)
SDRAM_A1: U1.M19 (PCLKC3_0), U2.24 (A1)
SDRAM_A2: U1.L20 (PCLKT3_1), U2.25 (A2)
SDRAM_A3: U1.L19 (PCLKT3_0), U2.26 (A3)
SDRAM_A4: U1.K20 (PCLKC2_0), U2.29 (A4)
SDRAM_A5: U1.K19 (PCLKC2_1), U2.30 (A5)
SDRAM_A6: U1.K18 (PR41D), U2.31 (A6)
SDRAM_A7: U1.J20 (PCLKT2_0), U2.32 (A7)
SDRAM_A8: U1.J19 (PCLKT2_1), U2.33 (A8)
SDRAM_A9: U1.H20 (PR41B), U2.34 (A9)
SDRAM_A10: U1.N19 (PR83A), U2.22 (A10)
SDRAM_A11: U1.G20 (PR38D), U2.35 (A11)
SDRAM_A12: U1.G19 (GR_PCLK2_1), U2.36 (A12)
SDRAM_BA0: U1.P19 (PR83C), U2.20 (BA0)
SDRAM_BA1: U1.N20 (PR83B), U2.21 (BA1)
SDRAM_CKE: U1.F20 (PR38C), U2.37 (CKE)
SDRAM_CLK: U1.F19 (PR38B), U2.38 (CLK)
SDRAM_D0: U1.J16 (PR20D), U2.2 (DQ0)
SDRAM_D1: U1.L18 (GR_PCLK3_1), U2.4 (DQ1)
SDRAM_D2: U1.M18 (PR50D), U2.5 (DQ2)
SDRAM_D3: U1.N18 (PR53C), U2.7 (DQ3)
SDRAM_D4: U1.P18 (PR83D), U2.8 (DQ4)
SDRAM_D5: U1.T18 (PR89D), U2.10 (DQ5)
SDRAM_D6: U1.T17 (GPLL0C_IN), U2.11 (DQ6)
SDRAM_D7: U1.U20 (PR86D), U2.13 (DQ7)
SDRAM_D8: U1.E19 (PR35D), U2.42 (DQ8)
SDRAM_D9: U1.D20 (VREF1_2), U2.44 (DQ9)
SDRAM_D10: U1.D19 (PR35B), U2.45 (DQ10)
SDRAM_D11: U1.C20 (PR35A), U2.47 (DQ11)
SDRAM_D12: U1.E18 (PR14C), U2.48 (DQ12)
SDRAM_D13: U1.F18 (PR14D), U2.50 (DQ13)
SDRAM_D14: U1.J18 (GR_PCLK2_0), U2.51 (DQ14)
SDRAM_D15: U1.J17 (PR20C), U2.53 (DQ15)
SDRAM_DQM0: U1.U19 (PR89C), U2.15 (DQML)
SDRAM_DQM1: U1.E20 (PR38A), U2.39 (DQMH)
SDRAM_nCAS: U1.T19 (PR89A), U2.17 (~CAS)
SDRAM_nCS: U1.P20 (PR86A), U2.19 (~CS)
SDRAM_nRAS: U1.R20 (PR86B), U2.18 (~RAS)
SDRAM_nWE: U1.T20 (PR86C), U2.16 (~WE)
SD_CLK: U1.T16 (PR77A); also elsewhere on the board
SD_CMD: U1.R17 (PR56D); also elsewhere on the board
SD_D0: U1.U16 (GPLL0T_IN); also elsewhere on the board
SD_D1: U1.R16 (PR56C); also elsewhere on the board
SD_D2: U1.U17 (PR92B); also elsewhere on the board
SD_D3: U1.U18 (PR92A); also elsewhere on the board
SHUTDOWN: U1.G16 (PR17C); also elsewhere on the board
SRV_PWM6: U1.D17 (PR11B); also elsewhere on the board
TOF_INT: U1.N17 (PR56A); also elsewhere on the board
TOF_XSHUT: U1.N16 (PR53A); also elsewhere on the board
USB_FPGA_D+: U1.E16 (PR11C)
USB_FPGA_D-: U1.F16 (PR11D)
